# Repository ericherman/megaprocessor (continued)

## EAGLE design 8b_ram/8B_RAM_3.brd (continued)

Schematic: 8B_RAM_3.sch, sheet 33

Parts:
D49, D50: L-1334SRT; LED3MM
Q433, Q434, Q435, Q436, Q437, Q438, Q439, Q440, Q441, Q442, Q443, Q444, Q445, Q446, Q447, Q448, Q449, Q450, Q734, Q735: 2N7000; TO92-DGS
R241, R242, R243, R244, R246, R247, R248, R249, R463, R464: 10k; R_P2INCH
R245, R250: 470; R_P2INCH

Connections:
+5V: D49.A, D50.A, R241.2, R242.2, R243.2, R244.2, R246.2, R247.2, R248.2, R249.2, R463.2, R464.2; also elsewhere on the board
B6_0: Q437.G, Q439.D, R244.1, R245.1
B6_0_N: Q438.D, Q439.G, Q449.G, R243.1
B6_1: Q445.G, Q447.D, R249.1, R250.1
B6_1_N: Q446.D, Q447.G, Q450.G, R248.1
BSEL6_N: Q734.G, Q735.G; also elsewhere on the board
GND: Q433.S, Q435.S, Q437.S, Q440.S, Q441.S, Q443.S, Q445.S, Q448.S, Q449.S, Q450.S, Q734.S, Q735.S; also elsewhere on the board
unnamed: Q433.D, Q434.S
unnamed: Q435.D, Q436.S
unnamed: Q437.D, Q438.S
unnamed: Q434.D, Q436.G, Q438.G, R241.1
unnamed: Q436.D, Q440.G, R242.1
unnamed: D49.K (C), R245.2
unnamed: Q439.S, Q440.D
unnamed: Q441.D, Q442.S
unnamed: Q443.D, Q444.S
unnamed: Q445.D, Q446.S
unnamed: Q442.D, Q444.G, Q446.G, R246.1
unnamed: Q444.D, Q448.G, R247.1
unnamed: D50.K (C), R250.2
unnamed: Q447.S, Q448.D
RD_6_0: Q449.D, Q734.D, R463.1; also elsewhere on the board
RD_6_1: Q450.D, Q735.D, R464.1; also elsewhere on the board
WD0: Q434.G; also elsewhere on the board
WD1: Q442.G; also elsewhere on the board
WR_BYTE6: Q433.G, Q435.G, Q441.G, Q443.G; also elsewhere on the board

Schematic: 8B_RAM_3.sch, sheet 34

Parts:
D51, D52: L-1334SRT; LED3MM
Q451, Q452, Q453, Q454, Q455, Q456, Q457, Q458, Q459, Q460, Q461, Q462, Q463, Q464, Q465, Q466, Q467, Q468, Q736, Q737: 2N7000; TO92-DGS
R251, R252, R253, R254, R256, R257, R258, R259, R465, R466: 10k; R_P2INCH
R255, R260: 470; R_P2INCH

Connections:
+5V: D51.A, D52.A, R251.2, R252.2, R253.2, R254.2, R256.2, R257.2, R258.2, R259.2, R465.2, R466.2; also elsewhere on the board
B6_2: Q455.G, Q457.D, R254.1, R255.1
B6_2_N: Q456.D, Q457.G, Q467.G, R253.1
B6_3: Q463.G, Q465.D, R259.1, R260.1
B6_3_N: Q464.D, Q465.G, Q468.G, R258.1
BSEL6_N: Q736.G, Q737.G; also elsewhere on the board
GND: Q451.S, Q453.S, Q455.S, Q458.S, Q459.S, Q461.S, Q463.S, Q466.S, Q467.S, Q468.S, Q736.S, Q737.S; also elsewhere on the board
unnamed: Q451.D, Q452.S
unnamed: Q453.D, Q454.S
unnamed: Q455.D, Q456.S
unnamed: Q452.D, Q454.G, Q456.G, R251.1
unnamed: Q454.D, Q458.G, R252.1
unnamed: D51.K (C), R255.2
unnamed: Q457.S, Q458.D
unnamed: Q459.D, Q460.S
unnamed: Q461.D, Q462.S
unnamed: Q463.D, Q464.S
unnamed: Q460.D, Q462.G, Q464.G, R256.1
unnamed: Q462.D, Q466.G, R257.1
unnamed: D52.K (C), R260.2
unnamed: Q465.S, Q466.D
RD_6_2: Q467.D, Q736.D, R465.1; also elsewhere on the board
RD_6_3: Q468.D, Q737.D, R466.1; also elsewhere on the board
WD2: Q452.G; also elsewhere on the board
WD3: Q460.G; also elsewhere on the board
WR_BYTE6: Q451.G, Q453.G, Q459.G, Q461.G; also elsewhere on the board

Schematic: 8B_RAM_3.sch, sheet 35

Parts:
D53, D54: L-1334SRT; LED3MM
Q469, Q470, Q471, Q472, Q473, Q474, Q475, Q476, Q477, Q478, Q479, Q480, Q481, Q482, Q483, Q484, Q485, Q486, Q738, Q739: 2N7000; TO92-DGS
R261, R262, R263, R264, R266, R267, R268, R269, R467, R468: 10k; R_P2INCH
R265, R270: 470; R_P2INCH

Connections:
+5V: D53.A, D54.A, R261.2, R262.2, R263.2, R264.2, R266.2, R267.2, R268.2, R269.2, R467.2, R468.2; also elsewhere on the board
B6_4: Q473.G, Q475.D, R264.1, R265.1
B6_4_N: Q474.D, Q475.G, Q485.G, R263.1
B6_5: Q481.G, Q483.D, R269.1, R270.1
B6_5_N: Q482.D, Q483.G, Q486.G, R268.1
BSEL6_N: Q738.G, Q739.G; also elsewhere on the board
GND: Q469.S, Q471.S, Q473.S, Q476.S, Q477.S, Q479.S, Q481.S, Q484.S, Q485.S, Q486.S, Q738.S, Q739.S; also elsewhere on the board
unnamed: Q469.D, Q470.S
unnamed: Q471.D, Q472.S
unnamed: Q473.D, Q474.S
unnamed: Q470.D, Q472.G, Q474.G, R261.1
unnamed: Q472.D, Q476.G, R262.1
unnamed: D53.K (C), R265.2
unnamed: Q475.S, Q476.D
unnamed: Q477.D, Q478.S
unnamed: Q479.D, Q480.S
unnamed: Q481.D, Q482.S
unnamed: Q478.D, Q480.G, Q482.G, R266.1
unnamed: Q480.D, Q484.G, R267.1
unnamed: D54.K (C), R270.2
unnamed: Q483.S, Q484.D
RD_6_4: Q485.D, Q738.D, R467.1; also elsewhere on the board
RD_6_5: Q486.D, Q739.D, R468.1; also elsewhere on the board
WD4: Q470.G; also elsewhere on the board
WD5: Q478.G; also elsewhere on the board
WR_BYTE6: Q469.G, Q471.G, Q477.G, Q479.G; also elsewhere on the board

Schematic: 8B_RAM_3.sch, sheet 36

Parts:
D55, D56: L-1334SRT; LED3MM
Q487, Q488, Q489, Q490, Q491, Q492, Q493, Q494, Q495, Q496, Q497, Q498, Q499, Q500, Q501, Q502, Q503, Q504, Q740, Q741: 2N7000; TO92-DGS
R271, R272, R273, R274, R276, R277, R278, R279, R469, R470: 10k; R_P2INCH
R275, R280: 470; R_P2INCH

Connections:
+5V: D55.A, D56.A, R271.2, R272.2, R273.2, R274.2, R276.2, R277.2, R278.2, R279.2, R469.2, R470.2; also elsewhere on the board
B6_6: Q491.G, Q493.D, R274.1, R275.1
B6_6_N: Q492.D, Q493.G, Q503.G, R273.1
B6_7: Q499.G, Q501.D, R279.1, R280.1
B6_7_N: Q500.D, Q501.G, Q504.G, R278.1
BSEL6_N: Q740.G, Q741.G; also elsewhere on the board
GND: Q487.S, Q489.S, Q491.S, Q494.S, Q495.S, Q497.S, Q499.S, Q502.S, Q503.S, Q504.S, Q740.S, Q741.S; also elsewhere on the board
unnamed: Q487.D, Q488.S
unnamed: Q489.D, Q490.S
unnamed: Q491.D, Q492.S
unnamed: Q488.D, Q490.G, Q492.G, R271.1
unnamed: Q490.D, Q494.G, R272.1
unnamed: D55.K (C), R275.2
unnamed: Q493.S, Q494.D
unnamed: Q495.D, Q496.S
unnamed: Q497.D, Q498.S
unnamed: Q499.D, Q500.S
unnamed: Q496.D, Q498.G, Q500.G, R276.1
unnamed: Q498.D, Q502.G, R277.1
unnamed: D56.K (C), R280.2
unnamed: Q501.S, Q502.D
RD_6_6: Q503.D, Q740.D, R469.1; also elsewhere on the board
RD_6_7: Q504.D, Q741.D, R470.1; also elsewhere on the board
WD6: Q488.G; also elsewhere on the board
WD7: Q496.G; also elsewhere on the board
WR_BYTE6: Q487.G, Q489.G, Q495.G, Q497.G; also elsewhere on the board

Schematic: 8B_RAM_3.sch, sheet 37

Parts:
D57, D58: L-1334SRT; LED3MM
Q505, Q506, Q507, Q508, Q509, Q510, Q511, Q512, Q513, Q514, Q515, Q516, Q517, Q518, Q519, Q520, Q521, Q522, Q742, Q743: 2N7000; TO92-DGS
R281, R282, R283, R284, R286, R287, R288, R289, R471, R472: 10k; R_P2INCH
R285, R290: 470; R_P2INCH

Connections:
+5V: D57.A, D58.A, R281.2, R282.2, R283.2, R284.2, R286.2, R287.2, R288.2, R289.2, R471.2, R472.2; also elsewhere on the board
B7_0: Q509.G, Q511.D, R284.1, R285.1
B7_0_N: Q510.D, Q511.G, Q521.G, R283.1
B7_1: Q517.G, Q519.D, R289.1, R290.1
B7_1_N: Q518.D, Q519.G, Q522.G, R288.1
BSEL7_N: Q742.G, Q743.G; also elsewhere on the board
GND: Q505.S, Q507.S, Q509.S, Q512.S, Q513.S, Q515.S, Q517.S, Q520.S, Q521.S, Q522.S, Q742.S, Q743.S; also elsewhere on the board
unnamed: Q505.D, Q506.S
unnamed: Q507.D, Q508.S
unnamed: Q509.D, Q510.S
unnamed: Q506.D, Q508.G, Q510.G, R281.1
unnamed: Q508.D, Q512.G, R282.1
unnamed: D57.K (C), R285.2
unnamed: Q511.S, Q512.D
unnamed: Q513.D, Q514.S
unnamed: Q515.D, Q516.S
unnamed: Q517.D, Q518.S
unnamed: Q514.D, Q516.G, Q518.G, R286.1
unnamed: Q516.D, Q520.G, R287.1
unnamed: D58.K (C), R290.2
unnamed: Q519.S, Q520.D
RD_7_0: Q521.D, Q743.D, R471.1; also elsewhere on the board
RD_7_1: Q522.D, Q742.D, R472.1; also elsewhere on the board
WD0: Q506.G; also elsewhere on the board
WD1: Q514.G; also elsewhere on the board
WR_BYTE7: Q505.G, Q507.G, Q513.G, Q515.G; also elsewhere on the board

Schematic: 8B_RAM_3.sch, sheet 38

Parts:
D59, D60: L-1334SRT; LED3MM
Q523, Q524, Q525, Q526, Q527, Q528, Q529, Q530, Q531, Q532, Q533, Q534, Q535, Q536, Q537, Q538, Q539, Q540, Q744, Q745: 2N7000; TO92-DGS
R291, R292, R293, R294, R296, R297, R298, R299, R473, R474: 10k; R_P2INCH
R295, R300: 470; R_P2INCH

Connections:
+5V: D59.A, D60.A, R291.2, R292.2, R293.2, R294.2, R296.2, R297.2, R298.2, R299.2, R473.2, R474.2; also elsewhere on the board
B7_2: Q527.G, Q529.D, R294.1, R295.1
B7_2_N: Q528.D, Q529.G, Q539.G, R293.1
B7_3: Q535.G, Q537.D, R299.1, R300.1
B7_3_N: Q536.D, Q537.G, Q540.G, R298.1
BSEL7_N: Q744.G, Q745.G; also elsewhere on the board
GND: Q523.S, Q525.S, Q527.S, Q530.S, Q531.S, Q533.S, Q535.S, Q538.S, Q539.S, Q540.S, Q744.S, Q745.S; also elsewhere on the board
unnamed: Q523.D, Q524.S
unnamed: Q525.D, Q526.S
unnamed: Q527.D, Q528.S
unnamed: Q524.D, Q526.G, Q528.G, R291.1
unnamed: Q526.D, Q530.G, R292.1
unnamed: D59.K (C), R295.2
unnamed: Q529.S, Q530.D
unnamed: Q531.D, Q532.S
unnamed: Q533.D, Q534.S
unnamed: Q535.D, Q536.S
unnamed: Q532.D, Q534.G, Q536.G, R296.1
unnamed: Q534.D, Q538.G, R297.1
unnamed: D60.K (C), R300.2
unnamed: Q537.S, Q538.D
RD_7_2: Q539.D, Q744.D, R473.1; also elsewhere on the board
RD_7_3: Q540.D, Q745.D, R474.1; also elsewhere on the board
WD2: Q524.G; also elsewhere on the board
WD3: Q532.G; also elsewhere on the board
WR_BYTE7: Q523.G, Q525.G, Q531.G, Q533.G; also elsewhere on the board

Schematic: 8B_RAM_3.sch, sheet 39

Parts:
D61, D62: L-1334SRT; LED3MM
Q541, Q542, Q543, Q544, Q545, Q546, Q547, Q548, Q549, Q550, Q551, Q552, Q553, Q554, Q555, Q556, Q557, Q558, Q746, Q747: 2N7000; TO92-DGS
R301, R302, R303, R304, R306, R307, R308, R309, R475, R476: 10k; R_P2INCH
R305, R310: 470; R_P2INCH

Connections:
+5V: D61.A, D62.A, R301.2, R302.2, R303.2, R304.2, R306.2, R307.2, R308.2, R309.2, R475.2, R476.2; also elsewhere on the board
B7_4: Q545.G, Q547.D, R304.1, R305.1
B7_4_N: Q546.D, Q547.G, Q557.G, R303.1
B7_5: Q553.G, Q555.D, R309.1, R310.1
B7_5_N: Q554.D, Q555.G, Q558.G, R308.1
BSEL7_N: Q746.G, Q747.G; also elsewhere on the board
GND: Q541.S, Q543.S, Q545.S, Q548.S, Q549.S, Q551.S, Q553.S, Q556.S, Q557.S, Q558.S, Q746.S, Q747.S; also elsewhere on the board
unnamed: Q541.D, Q542.S
unnamed: Q543.D, Q544.S
unnamed: Q545.D, Q546.S
unnamed: Q542.D, Q544.G, Q546.G, R301.1
unnamed: Q544.D, Q548.G, R302.1
unnamed: D61.K (C), R305.2
unnamed: Q547.S, Q548.D
unnamed: Q549.D, Q550.S
unnamed: Q551.D, Q552.S
unnamed: Q553.D, Q554.S
unnamed: Q550.D, Q552.G, Q554.G, R306.1
unnamed: Q552.D, Q556.G, R307.1
unnamed: D62.K (C), R310.2
unnamed: Q555.S, Q556.D
RD_7_4: Q557.D, Q747.D, R475.1; also elsewhere on the board
RD_7_5: Q558.D, Q746.D, R476.1; also elsewhere on the board
WD4: Q542.G; also elsewhere on the board
WD5: Q550.G; also elsewhere on the board
WR_BYTE7: Q541.G, Q543.G, Q549.G, Q551.G; also elsewhere on the board

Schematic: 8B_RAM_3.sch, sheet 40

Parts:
D63, D64: L-1334SRT; LED3MM
Q559, Q560, Q561, Q562, Q563, Q564, Q565, Q566, Q567, Q568, Q569, Q570, Q571, Q572, Q573, Q574, Q575, Q576, Q748, Q749: 2N7000; TO92-DGS
R311, R312, R313, R314, R316, R317, R318, R319, R477, R478: 10k; R_P2INCH
R315, R320: 470; R_P2INCH

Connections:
+5V: D63.A, D64.A, R311.2, R312.2, R313.2, R314.2, R316.2, R317.2, R318.2, R319.2, R477.2, R478.2; also elsewhere on the board
B7_6: Q563.G, Q565.D, R314.1, R315.1
B7_6_N: Q564.D, Q565.G, Q575.G, R313.1
B7_7: Q571.G, Q573.D, R319.1, R320.1
B7_7_N: Q572.D, Q573.G, Q576.G, R318.1
BSEL7_N: Q748.G, Q749.G; also elsewhere on the board
GND: Q559.S, Q561.S, Q563.S, Q566.S, Q567.S, Q569.S, Q571.S, Q574.S, Q575.S, Q576.S, Q748.S, Q749.S; also elsewhere on the board
unnamed: Q559.D, Q560.S
unnamed: Q561.D, Q562.S
unnamed: Q563.D, Q564.S
unnamed: Q560.D, Q562.G, Q564.G, R311.1
unnamed: Q562.D, Q566.G, R312.1
unnamed: D63.K (C), R315.2
unnamed: Q565.S, Q566.D
unnamed: Q567.D, Q568.S
unnamed: Q569.D, Q570.S
unnamed: Q571.D, Q572.S
unnamed: Q568.D, Q570.G, Q572.G, R316.1
unnamed: Q570.D, Q574.G, R317.1
unnamed: D64.K (C), R320.2
unnamed: Q573.S, Q574.D
RD_7_6: Q575.D, Q748.D, R477.1; also elsewhere on the board
RD_7_7: Q576.D, Q749.D, R478.1; also elsewhere on the board
WD6: Q560.G; also elsewhere on the board
WD7: Q568.G; also elsewhere on the board
WR_BYTE7: Q559.G, Q561.G, Q567.G, Q569.G; also elsewhere on the board

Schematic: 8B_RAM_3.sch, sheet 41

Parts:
Q597, Q614, Q624, Q631, Q638, Q645, Q652, Q659, Q756, Q758, Q759, Q760, Q761, Q762, Q763, Q764, Q765, Q766, Q767, Q769: 2N7000; TO92-DGS
R321, R322, R349, R359, R366, R370: 10k; R_P2INCH

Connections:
+5V: R321.2, R322.2, R349.2, R359.2, R366.2, R370.2; also elsewhere on the board
GND: Q597.S, Q614.S, Q624.S, Q631.S, Q638.S, Q645.S, Q652.S, Q659.S, Q756.S, Q758.S, Q759.S, Q760.S, Q761.S, Q762.S, Q763.S, Q764.S, Q765.S, Q766.S, Q767.S, Q769.S; also elsewhere on the board
MUXED_RD_0: Q756.D, Q758.G, R359.1
MUXED_RD_0_N: Q597.D, Q614.D, Q624.D, Q631.D, Q638.D, Q645.D, Q652.D, Q659.D, Q756.G, R349.1
MUXED_RD_1: Q767.D, Q769.G, R370.1
MUXED_RD_1_N: Q759.D, Q760.D, Q761.D, Q762.D, Q763.D, Q764.D, Q765.D, Q766.D, Q767.G, R366.1
RD0: Q758.D, R321.1; also elsewhere on the board
RD1: Q769.D, R322.1; also elsewhere on the board
RD_0_0: Q597.G; also elsewhere on the board
RD_0_1: Q759.G; also elsewhere on the board
RD_1_0: Q614.G; also elsewhere on the board
RD_1_1: Q760.G; also elsewhere on the board
RD_2_0: Q624.G; also elsewhere on the board
RD_2_1: Q761.G; also elsewhere on the board
RD_3_0: Q631.G; also elsewhere on the board
RD_3_1: Q762.G; also elsewhere on the board
RD_4_0: Q638.G; also elsewhere on the board
RD_4_1: Q763.G; also elsewhere on the board
RD_5_0: Q645.G; also elsewhere on the board
RD_5_1: Q764.G; also elsewhere on the board
RD_6_0: Q652.G; also elsewhere on the board
RD_6_1: Q765.G; also elsewhere on the board
RD_7_0: Q659.G; also elsewhere on the board
RD_7_1: Q766.G; also elsewhere on the board

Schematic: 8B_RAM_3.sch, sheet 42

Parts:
Q770, Q771, Q772, Q773, Q774, Q775, Q776, Q777, Q778, Q780, Q781, Q782, Q783, Q784, Q785, Q786, Q787, Q788, Q789, Q791: 2N7000; TO92-DGS
R323, R324, R374, R378, R382, R386: 10k; R_P2INCH

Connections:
+5V: R323.2, R324.2, R374.2, R378.2, R382.2, R386.2; also elsewhere on the board
GND: Q770.S, Q771.S, Q772.S, Q773.S, Q774.S, Q775.S, Q776.S, Q777.S, Q778.S, Q780.S, Q781.S, Q782.S, Q783.S, Q784.S, Q785.S, Q786.S, Q787.S, Q788.S, Q789.S, Q791.S; also elsewhere on the board
MUXED_RD_2: Q778.D, Q780.G, R378.1
MUXED_RD_2_N: Q770.D, Q771.D, Q772.D, Q773.D, Q774.D, Q775.D, Q776.D, Q777.D, Q778.G, R374.1
MUXED_RD_3: Q789.D, Q791.G, R386.1
MUXED_RD_3_N: Q781.D, Q782.D, Q783.D, Q784.D, Q785.D, Q786.D, Q787.D, Q788.D, Q789.G, R382.1
RD2: Q780.D, R323.1; also elsewhere on the board
RD3: Q791.D, R324.1; also elsewhere on the board
RD_0_2: Q770.G; also elsewhere on the board
RD_0_3: Q781.G; also elsewhere on the board
RD_1_2: Q771.G; also elsewhere on the board
RD_1_3: Q782.G; also elsewhere on the board
RD_2_2: Q772.G; also elsewhere on the board
RD_2_3: Q783.G; also elsewhere on the board
RD_3_2: Q773.G; also elsewhere on the board
RD_3_3: Q784.G; also elsewhere on the board
RD_4_2: Q774.G; also elsewhere on the board
RD_4_3: Q785.G; also elsewhere on the board
RD_5_2: Q775.G; also elsewhere on the board
RD_5_3: Q786.G; also elsewhere on the board
RD_6_2: Q776.G; also elsewhere on the board
RD_6_3: Q787.G; also elsewhere on the board
RD_7_2: Q777.G; also elsewhere on the board
RD_7_3: Q788.G; also elsewhere on the board

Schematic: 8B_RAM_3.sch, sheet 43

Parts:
Q792, Q793, Q794, Q795, Q796, Q797, Q798, Q799, Q800, Q802, Q803, Q804, Q805, Q806, Q807, Q808, Q809, Q810, Q811, Q813: 2N7000; TO92-DGS
R325, R326, R484, R485, R486, R487: 10k; R_P2INCH

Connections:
+5V: R325.2, R326.2, R484.2, R485.2, R486.2, R487.2; also elsewhere on the board
GND: Q792.S, Q793.S, Q794.S, Q795.S, Q796.S, Q797.S, Q798.S, Q799.S, Q800.S, Q802.S, Q803.S, Q804.S, Q805.S, Q806.S, Q807.S, Q808.S, Q809.S, Q810.S, Q811.S, Q813.S; also elsewhere on the board
MUXED_RD_4: Q800.D, Q802.G, R485.1
MUXED_RD_4_N: Q792.D, Q793.D, Q794.D, Q795.D, Q796.D, Q797.D, Q798.D, Q799.D, Q800.G, R484.1
MUXED_RD_5: Q811.D, Q813.G, R487.1
MUXED_RD_5_N: Q803.D, Q804.D, Q805.D, Q806.D, Q807.D, Q808.D, Q809.D, Q810.D, Q811.G, R486.1
RD4: Q802.D, R325.1; also elsewhere on the board
RD5: Q813.D, R326.1; also elsewhere on the board
RD_0_4: Q792.G; also elsewhere on the board
RD_0_5: Q803.G; also elsewhere on the board
RD_1_4: Q793.G; also elsewhere on the board
RD_1_5: Q804.G; also elsewhere on the board
RD_2_4: Q794.G; also elsewhere on the board
RD_2_5: Q805.G; also elsewhere on the board
RD_3_4: Q795.G; also elsewhere on the board
RD_3_5: Q806.G; also elsewhere on the board
RD_4_4: Q796.G; also elsewhere on the board
RD_4_5: Q807.G; also elsewhere on the board
RD_5_4: Q797.G; also elsewhere on the board
RD_5_5: Q808.G; also elsewhere on the board
RD_6_4: Q798.G; also elsewhere on the board
RD_6_5: Q809.G; also elsewhere on the board
RD_7_4: Q799.G; also elsewhere on the board
RD_7_5: Q810.G; also elsewhere on the board

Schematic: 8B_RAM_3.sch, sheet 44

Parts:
Q814, Q815, Q816, Q817, Q818, Q819, Q820, Q821, Q822, Q824, Q825, Q826, Q827, Q828, Q829, Q830, Q831, Q832, Q833, Q835: 2N7000; TO92-DGS
R327, R328, R488, R489, R490, R491: 10k; R_P2INCH

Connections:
+5V: R327.2, R328.2, R488.2, R489.2, R490.2, R491.2; also elsewhere on the board
GND: Q814.S, Q815.S, Q816.S, Q817.S, Q818.S, Q819.S, Q820.S, Q821.S, Q822.S, Q824.S, Q825.S, Q826.S, Q827.S, Q828.S, Q829.S, Q830.S, Q831.S, Q832.S, Q833.S, Q835.S; also elsewhere on the board
MUXED_RD_6: Q822.D, Q824.G, R489.1
MUXED_RD_6_N: Q814.D, Q815.D, Q816.D, Q817.D, Q818.D, Q819.D, Q820.D, Q821.D, Q822.G, R488.1
MUXED_RD_7: Q833.D, Q835.G, R491.1
MUXED_RD_7_N: Q825.D, Q826.D, Q827.D, Q828.D, Q829.D, Q830.D, Q831.D, Q832.D, Q833.G, R490.1
RD6: Q824.D, R327.1; also elsewhere on the board
RD7: Q835.D, R328.1; also elsewhere on the board
RD_0_6: Q814.G; also elsewhere on the board
RD_0_7: Q825.G; also elsewhere on the board
RD_1_6: Q815.G; also elsewhere on the board
RD_1_7: Q826.G; also elsewhere on the board
RD_2_6: Q816.G; also elsewhere on the board
RD_2_7: Q827.G; also elsewhere on the board
RD_3_6: Q817.G; also elsewhere on the board
RD_3_7: Q828.G; also elsewhere on the board
RD_4_6: Q818.G; also elsewhere on the board
RD_4_7: Q829.G; also elsewhere on the board
RD_5_6: Q819.G; also elsewhere on the board
RD_5_7: Q830.G; also elsewhere on the board
RD_6_6: Q820.G; also elsewhere on the board
RD_6_7: Q831.G; also elsewhere on the board
RD_7_6: Q821.G; also elsewhere on the board
RD_7_7: Q832.G; also elsewhere on the board

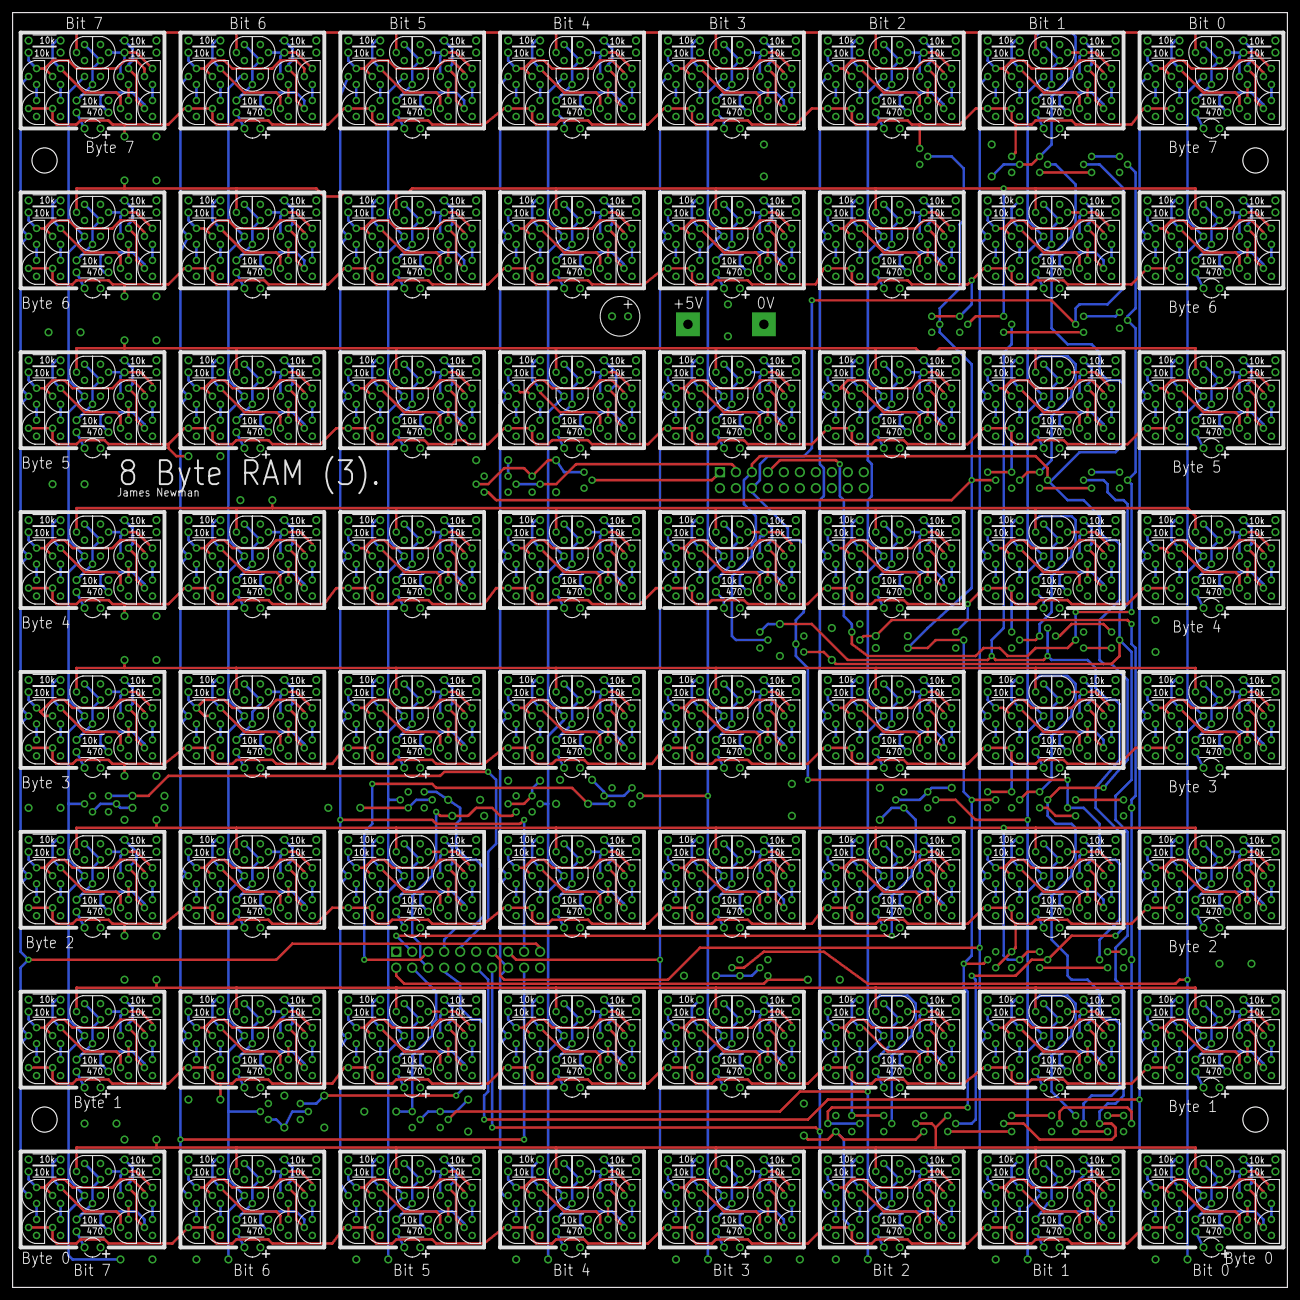
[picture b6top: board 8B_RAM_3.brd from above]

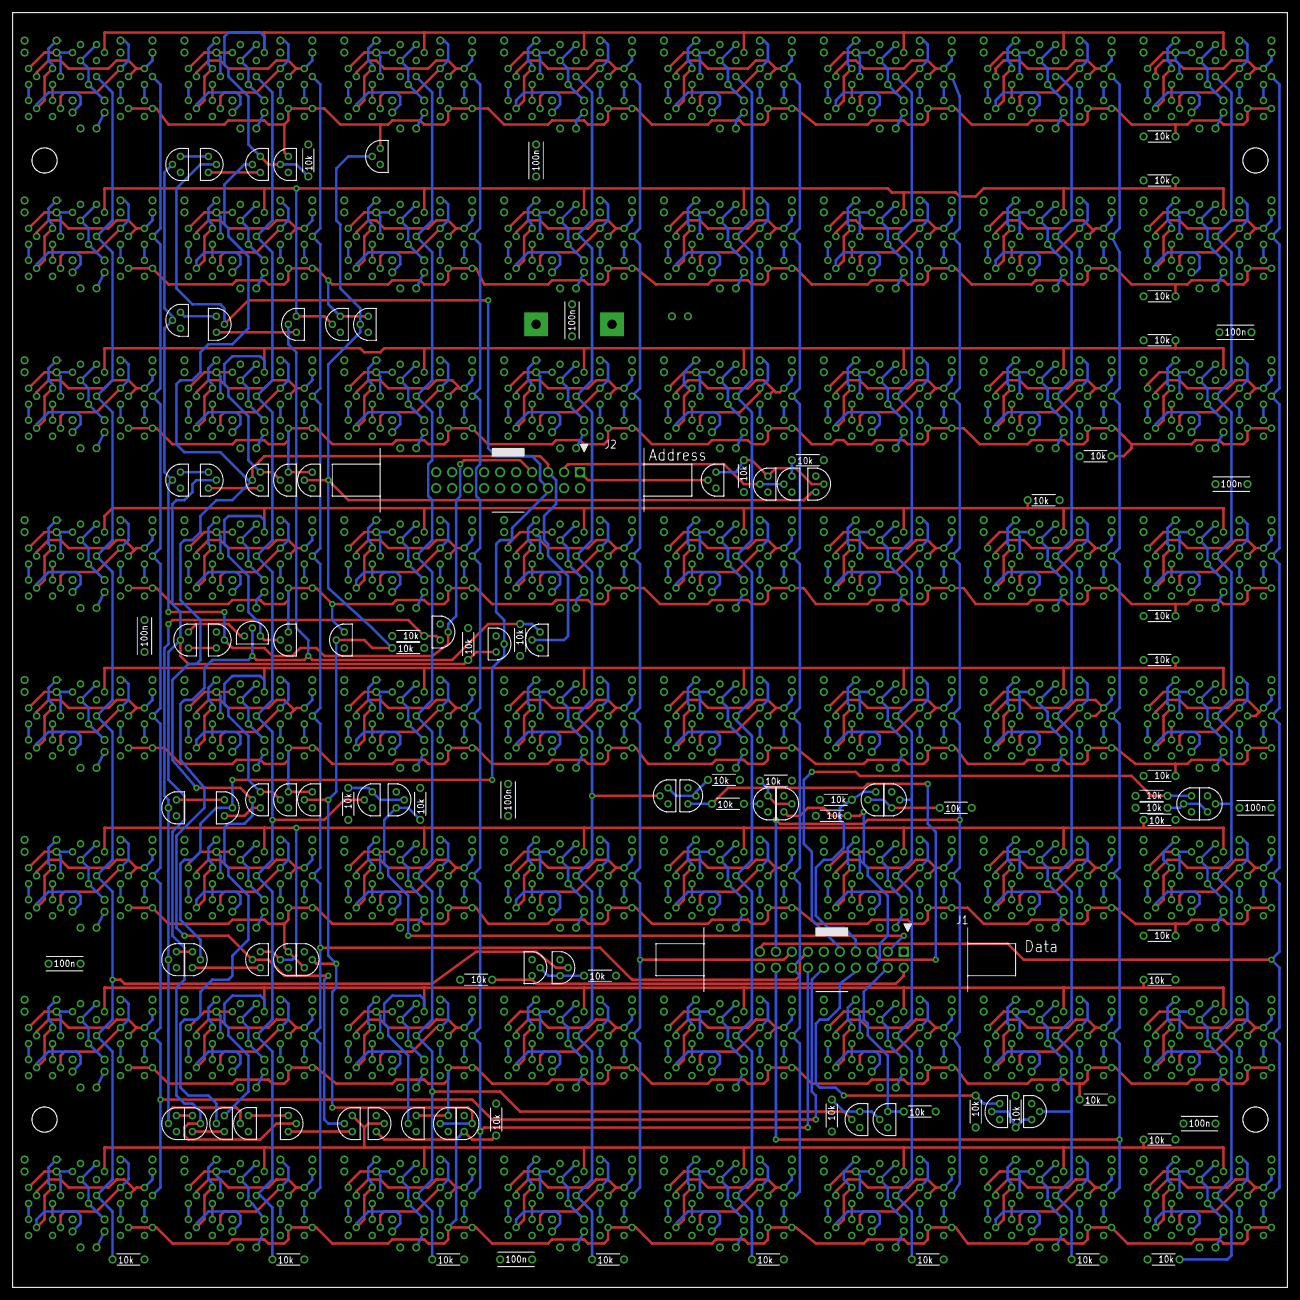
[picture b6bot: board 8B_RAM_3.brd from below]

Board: 4 copper layers, 202.6 x 202.6 mm, 1280 parts (121 on the bottom side), 717 nets.
